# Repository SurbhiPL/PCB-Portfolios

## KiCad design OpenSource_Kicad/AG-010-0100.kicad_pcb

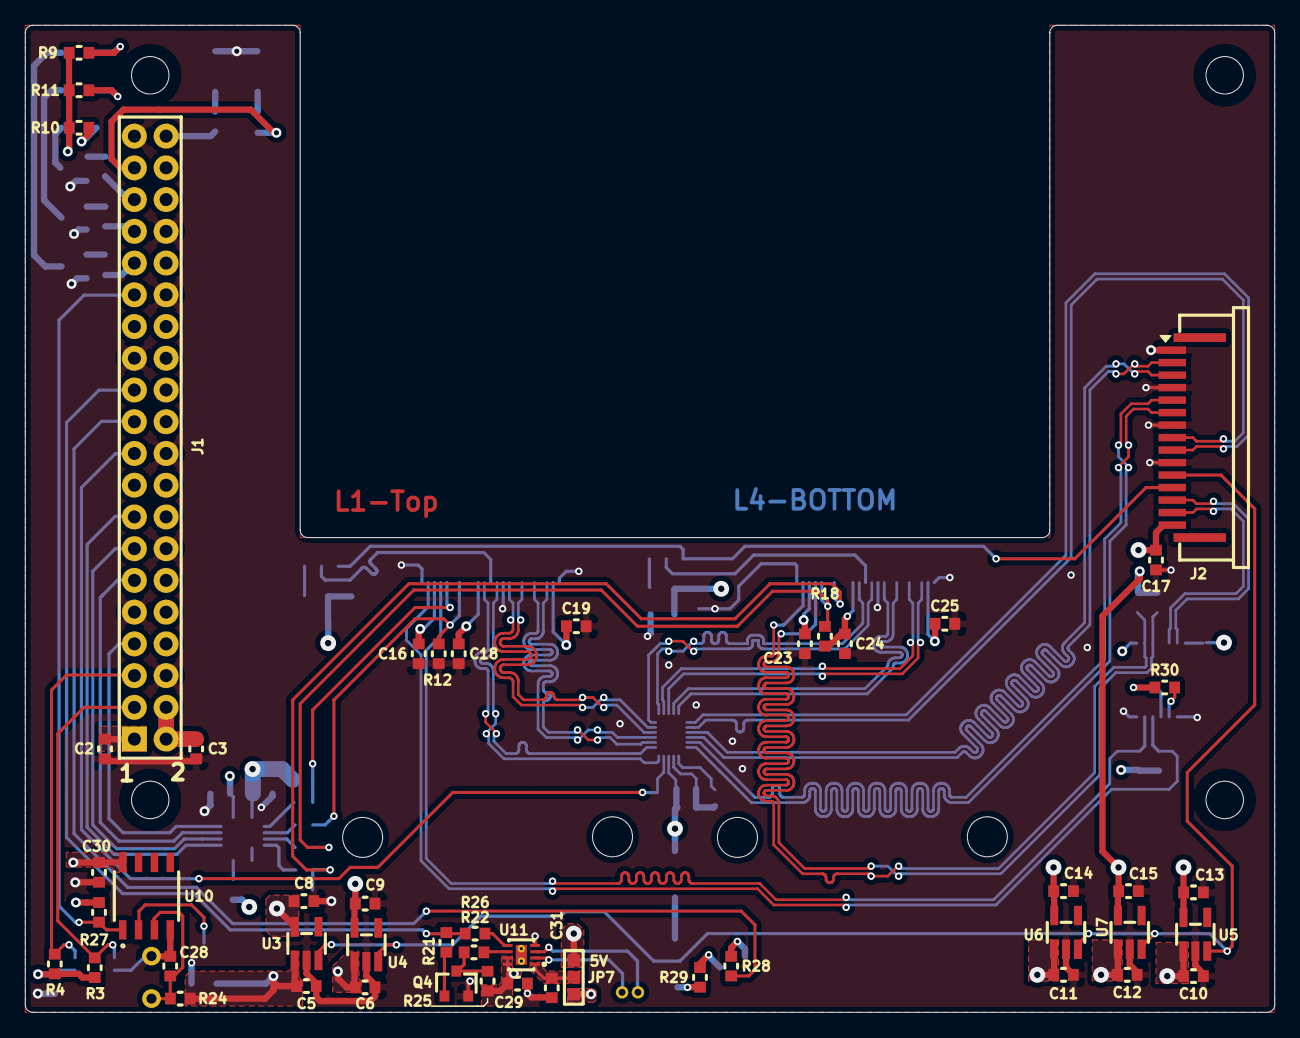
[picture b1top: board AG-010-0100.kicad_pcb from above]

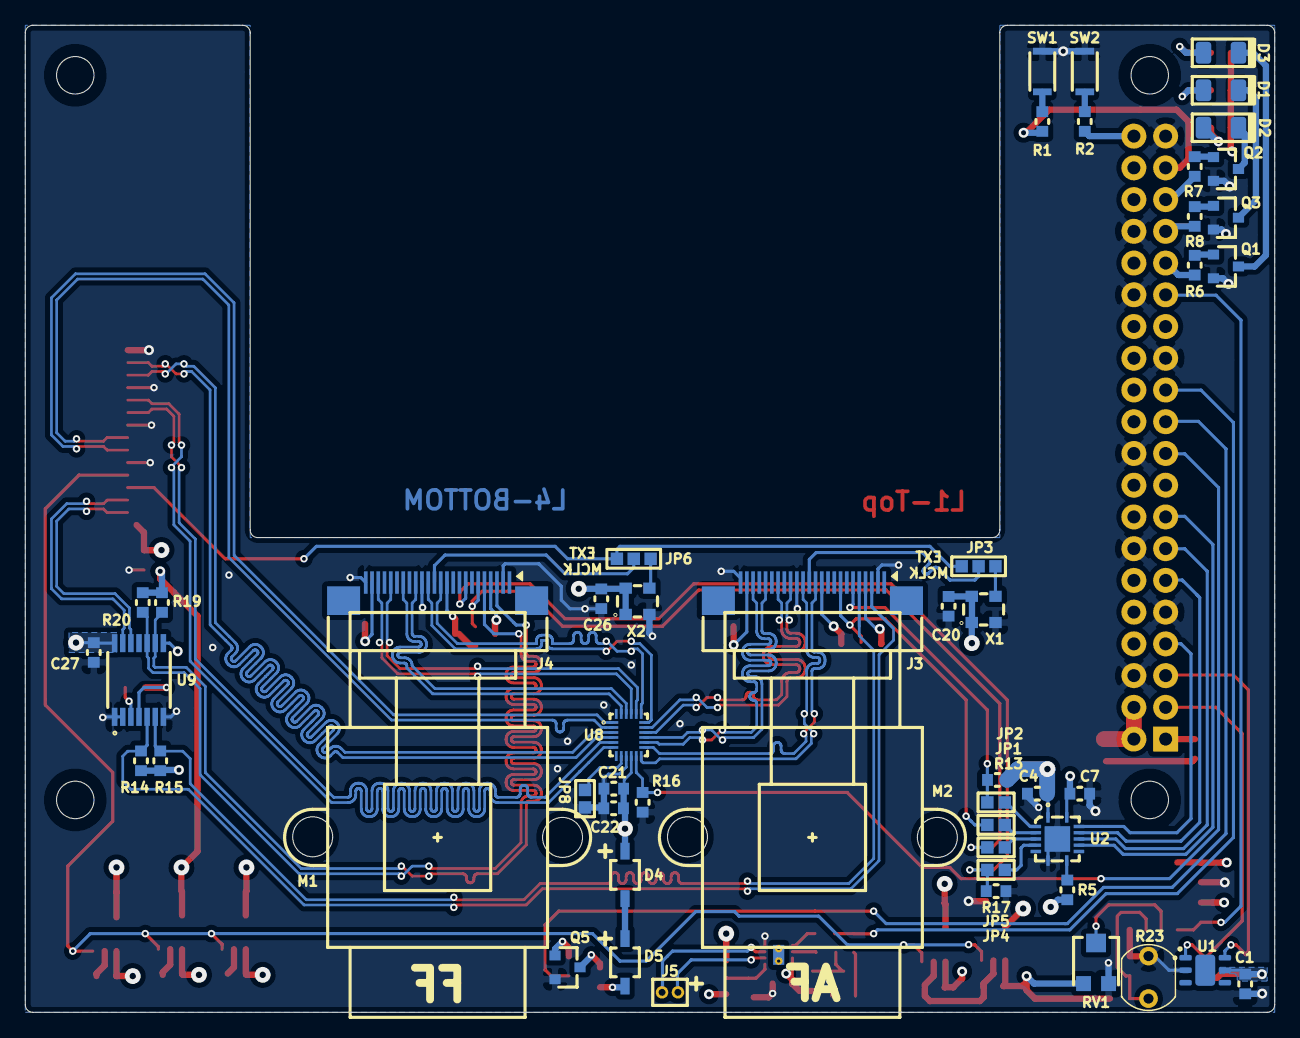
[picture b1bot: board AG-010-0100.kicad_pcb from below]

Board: 4 copper layers, 100.0 x 79.0 mm, 106 parts (52 on the bottom side), 88 nets.

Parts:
C1, C2, C3, C4, C7, C16, C18, C19, C21, C23, C24, C25, C27, C28, C29, C30, C31: 0.1uF; C0603
C5, C6, C8, C9, C10, C11, C12, C13, C14, C15, C17, C20, C26: 1uF; C0603
C22: 10uF; C0603
D1: 150120RS75000; LED_1206RED
D2, D3: 150120BS75000; LED_1206BLU
D4, D5: VSMG285011G; LED-SMD-2-GULl-WING
H1, H2, H3, H4: HOLE; HOLE_3MM
J1: ESW-120-44-T-D; nVidia-Jetson-nano
J2: SFW15R-1STE1LF; CON-1X15-P1-(SFW15R-1STE1LF)
J3, J4: SFV24R-3STBE1HLF; OV5640
J5: M50-3530242; PINHD-M1X2-P1.27-(M50-3530242)
JP1, JP2, JP4, JP5, JP8: Jumper_Sholder_2PinOpen; JUMP_2PIN_OPEN
JP3, JP6, JP7: Jumper_Sholder_3PinOpen; JUMP_3PIN_OPEN
M1, M2: IR_Switch
Q1, Q2, Q3, Q4, Q5: MMBT3904; SOT-23
R1, R2, R9: 100R; R0603
R3, R4, R5, R16, R24, R25, R27, R30: 10K; R0603
R6, R7, R8, R21, R28: 1K; R0603
R10, R11: 10R; R0603
R12, R13, R14, R15, R17, R18, R19, R20: 2.2K; R0603
R22, R26: 22R; R0603
R23: LDR; LDR_5.1x4.3_RM3.4
R29: 3.3R; R0603
RV1: TC33X-2-103E; TC33X-2_TRIMPOT
SW1, SW2: TL3780AF240QG; TACT_SMD_TL3780
U1: SI7006-A20-IMR; DFN-6-1EP_3x3mm_P1mm_EP1.5x2.4mm
U2: TXB0104RGY; VQFN-14_EP
U3, U5, U6: AP7331-28WG-7; SOT-23-5
U4, U7: AP7331-18WG-7; SOT-23-5
U8: FSA642UMX; UMLP-24-3.4X2.5
U9: PCA9543APW,118; TSSOP-14_4.4x5mm_P0.65mm
U10: LM393ADR; SOIC-8_3.9x4.9_P1.27
U11: DRV8837DSGR; WSON-8-1EP_2x2mm_P0.5mm_EP0.9x1.6mm_ThermalVias
X1, X2: DSC6003CI2A-024.0000; XTAL-4-3.2X2.5

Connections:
+1V8A: C4.1, C9.1, C18.1, C20.1, J3.11, R5.1, R13.1, R14.1, R15.1, U2.1, U4.5, X1.1, X1.4
+1V8B: C15.1, C24.1, C26.1, J4.11, R18.1, R19.1, R20.1, U7.5, X2.1, X2.4
+2V8A: C8.1, C16.1, J3.4, U3.5
+2V8B: C14.1, C23.1, J4.4, U6.5
+3V3_Nano: C1.1, C2.1, C5.1, C6.1, C7.1, C10.1, C11.1, C12.1, C17.1, C21.1, C22.1, C27.1, C29.1, C30.1, D4.2, J1.1, J1.17, J2.15, JP7.1, R3.1, R4.1, R9.1, R10.1, R11.1, R24.2, R25.1, R27.2, R30.2, RV1.1, U1.5, U2.14, U3.1, U4.1, U5.1, U6.1, U7.1, U8.10, U9.4, U9.8, U9.14, U10.8, U11.7, U11.8
+5V: C3.1, J1.2, J1.4, JP7.3
+AF_2V8: C13.1, C19.1, C25.1, J3.23, J4.23, U5.5
CAM1_MCLK: J3.13, JP3.2
CAM1_MC_N: J3.18, U8.16
CAM1_MC_P: J3.16, U8.17
CAM1_MD0_N: J3.22, U8.14
CAM1_MD0_P: J3.20, U8.15
CAM1_MD1_N: J3.14, U8.12
CAM1_MD1_P: J3.12, U8.13
CAM1_PWDN: J1.11, U2.12
CAM1_RST: J1.7, U2.13
CAM2_MCLK: J4.13, JP6.2
CAM2_MC_N: J4.18, U8.23
CAM2_MC_P: J4.16, U8.22
CAM2_MD0_N: J4.22, U8.21
CAM2_MD0_P: J4.20, U8.20
CAM2_MD1_N: J4.14, U8.18
CAM2_MD1_P: J4.12, U8.19
CAM2_PWDN: J1.15, U2.10
CAM2_RST: J1.13, U2.11
CLK_N: J2.8, U8.2
CLK_P: J2.9, U8.1
D0_N: J2.2, U8.4
D0_P: J2.3, U8.3
D1_N: J2.5, U8.6
D1_P: J2.6, U8.5
ENABLE: J2.11, U3.3, U4.3, U5.3, U6.3, U7.3
GND: C1.2, C2.2, C3.2, C4.2, C5.2, C6.2, C7.2, C8.2, C9.2, C10.2, C11.2, C12.2, C13.2, C14.2, C15.2, C16.2, C17.2, C18.2, C19.2, C20.2, C21.2, C22.2, C23.2, C24.2, C25.2, C26.2, C27.2, C28.2, C29.2, C30.2, C31.2, J1.6, J1.9, J1.14, J1.20, J1.25, J1.30, J1.34, J1.39, J2.1, J2.4, J2.7, J2.10, J3.2, J3.15, J3.24, J4.2, J4.15, J4.24, JP8.2, Q1.2, Q2.2, Q3.2, Q4.2, Q5.2, R12.2, R16.1, R17.2, R23.2, RV1.3, SW1.2, SW2.2, U1.2, U2.7, U2.15, U3.2, U4.2, U5.2, U6.2, U7.2, U8.9, U9.1, U9.2, U9.7, U10.4, U11.4, X1.2, X2.2
I2C1_N: J3.5, R15.2, U9.6
I2C1_P: J3.3, R14.2, U9.5
I2C2_N: J4.5, R20.2, U9.10
I2C2_P: J4.3, R19.2, U9.9
I2C2_SCL: J1.5, R4.2, U1.6
I2C2_SDA: J1.3, R3.2, U1.1
I2CIN_N: J2.13, U9.13
I2CIN_P: J2.14, U9.12
IR_LED: J1.21, R28.1
LDR: J1.29, R27.1, U10.1
LED1: J1.31, R6.2
LED2: J1.35, R7.2
LED3: J1.33, R8.2
MCLK: J2.12, JP3.3, JP6.3
unnamed: C28.1, R23.1, R24.1, U10.3
unnamed: C31.1, JP7.2, U11.1
unnamed: D1.1, Q3.3
unnamed: D1.2, R11.2
unnamed: D2.1, Q2.3
unnamed: D2.2, R10.2
unnamed: D3.1, Q1.3
unnamed: D3.2, R9.2
unnamed: D4.1, D5.2
unnamed: D5.1, R29.2
unnamed: J3.6, JP1.2, R13.2
unnamed: J3.8, JP2.2, R12.1
unnamed: J4.6, JP4.2, R18.2
unnamed: J4.8, JP5.2, R17.1
unnamed: J5.1, U11.2
unnamed: J5.2, U11.3
unnamed: JP3.1, X1.3
unnamed: JP6.1, X2.3
unnamed: JP8.1, U8.8
unnamed: Q1.1, R6.1
unnamed: Q2.1, R7.1
unnamed: Q3.1, R8.1
unnamed: Q4.1, R21.2
unnamed: Q4.3, R25.2, R26.1
unnamed: Q5.1, R28.2
unnamed: Q5.3, R29.1
unnamed: R1.2, SW1.1
unnamed: R2.2, SW2.1
unnamed: R5.2, U2.8
unnamed: R22.2, U11.5
unnamed: R26.2, U11.6
unnamed: R30.1, U9.3
unnamed: RV1.2, U10.2
PWDN_CAM1: JP2.1, U2.3
PWDN_CAM2: JP5.1, U2.5
RST_CAM1: JP1.1, U2.2
RST_CAM2: JP4.1, U2.4
SW1: J1.37, R1.1
SW2: J1.40, R2.1
SW_IR: J1.23, R21.1, R22.1
SW_MIPI: J1.19, R16.2, U8.11

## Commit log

2022-08-14 First commit
    First commit
